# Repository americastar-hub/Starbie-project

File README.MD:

THIS IS MY CUTSOM VIRTUSAL PET PROJECT  FOR WEEK 1
PIC

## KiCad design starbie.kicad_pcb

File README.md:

this is WEEK 1 of my starbie all i did this week was coding it and i can not do much till i get the kit

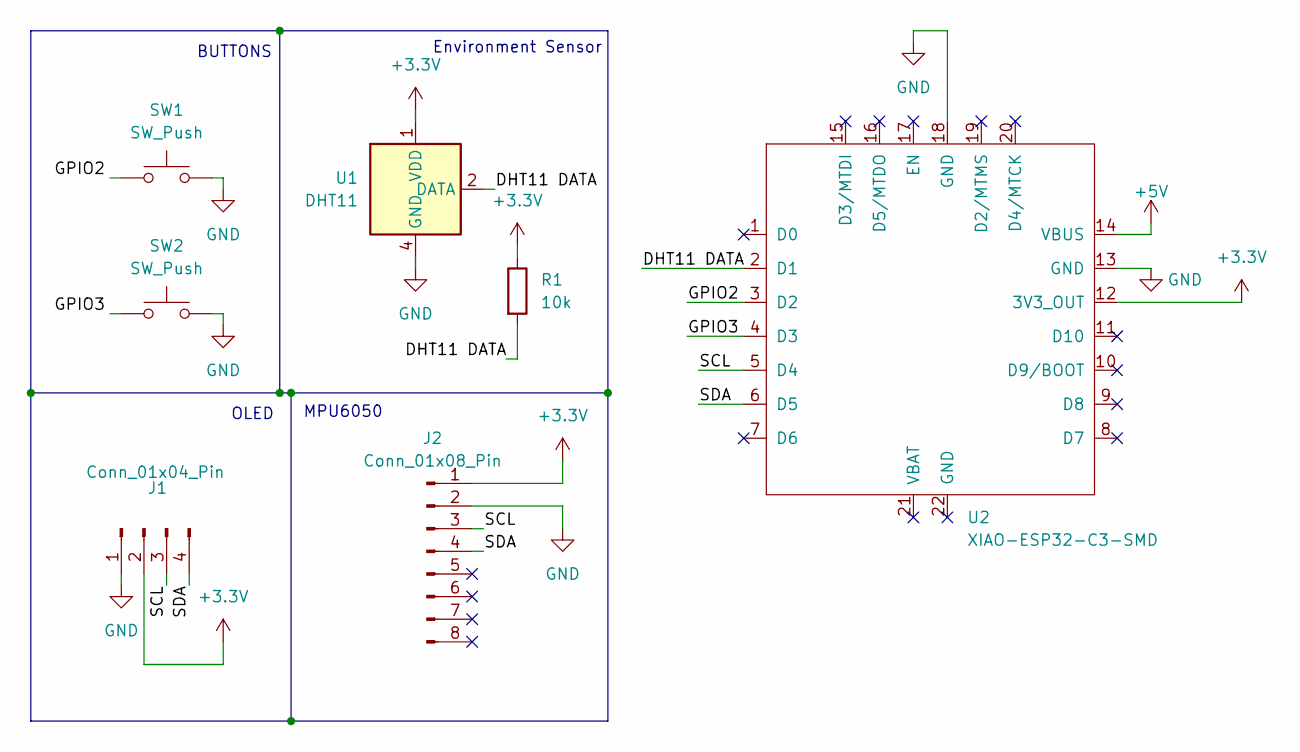
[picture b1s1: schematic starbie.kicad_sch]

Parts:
J1: Conn_01x04_Pin; Display_128x64_096_I2C
J2: Conn_01x08_Pin; PinHeader_1x08_P2.54mm_Vertical
R1: 10k; R_Axial_DIN0204_L3.6mm_D1.6mm_P2.54mm_Vertical
SW1, SW2: SW_Push; SW_Cherry_MX_1.00u_PCB
U1: DHT11; Aosong_DHT11_5.5x12.0_P2.54mm
U2: XIAO-ESP32-C3-SMD

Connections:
+3.3V: J1.2, J2.1, R1.1, U1.1 (VDD), U2.12 (3V3_OUT)
+5V: U2.14 (VBUS)
/DHT11 DATA: U1.2 (DATA), U2.2 (D1)
/GPIO2: U2.3 (D2)
/GPIO3: U2.4 (D3)
/SCL: J1.3, J2.3, U2.5 (D4)
/SDA: J1.4, J2.4, U2.6 (D5)
GND: J1.1, J2.2, SW1.2 (2_2), SW2.2 (2_2), U1.4 (GND), U2.13 (GND), U2.18 (GND)

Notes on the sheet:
MPU6050
OLED
Environment Sensor
BUTTONS

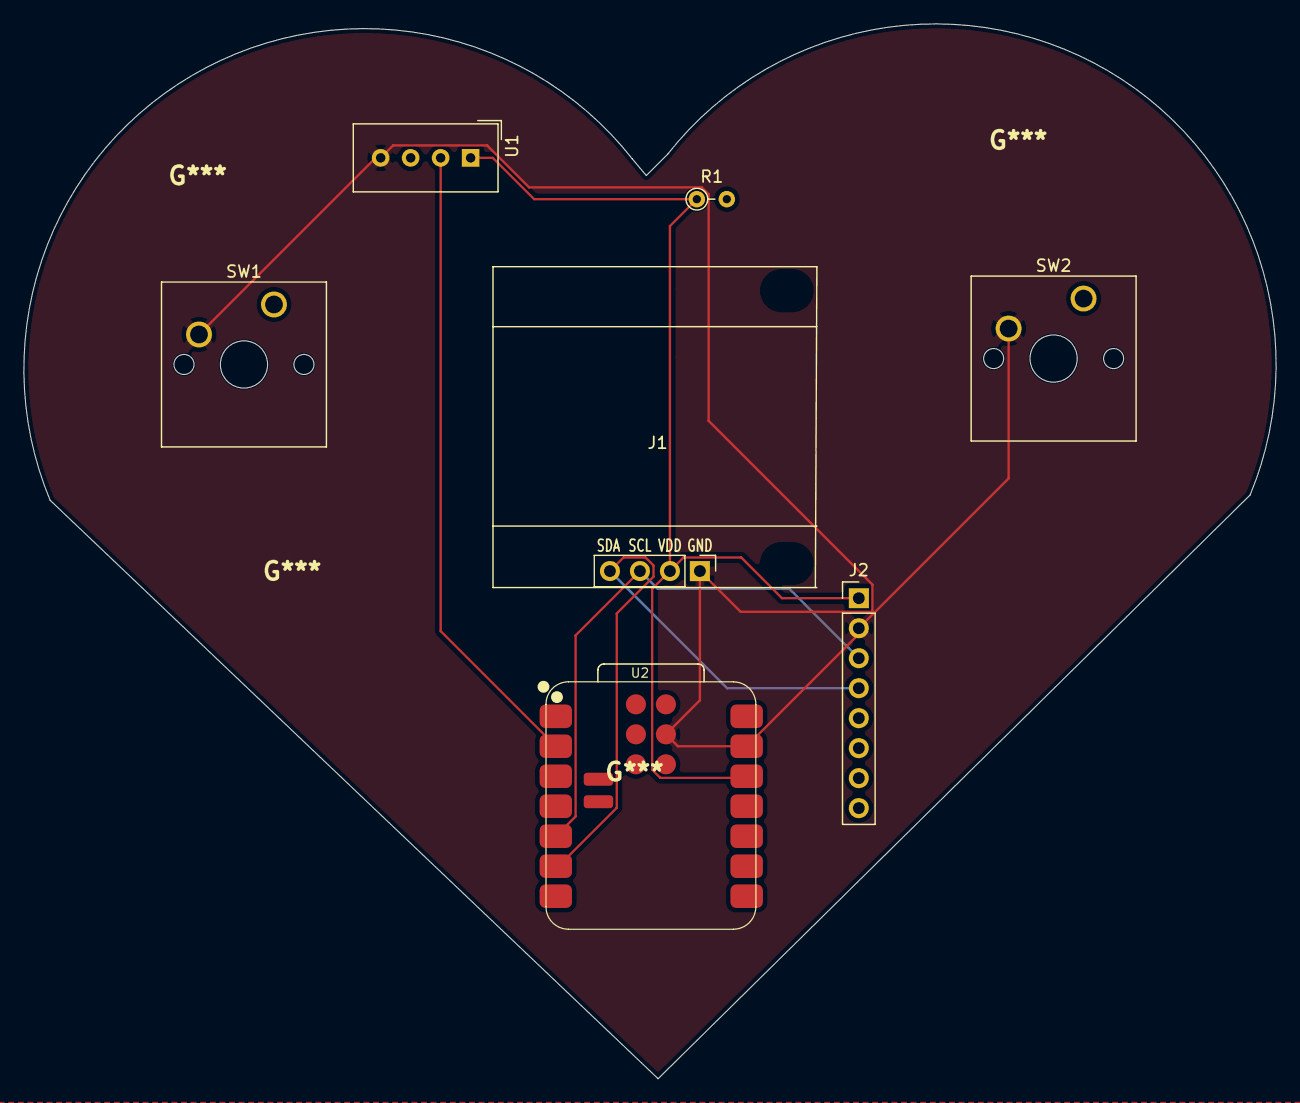
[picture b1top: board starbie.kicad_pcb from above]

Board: 2 copper layers, 106.1 x 89.3 mm, 7 parts (0 on the bottom side), 5 nets.
